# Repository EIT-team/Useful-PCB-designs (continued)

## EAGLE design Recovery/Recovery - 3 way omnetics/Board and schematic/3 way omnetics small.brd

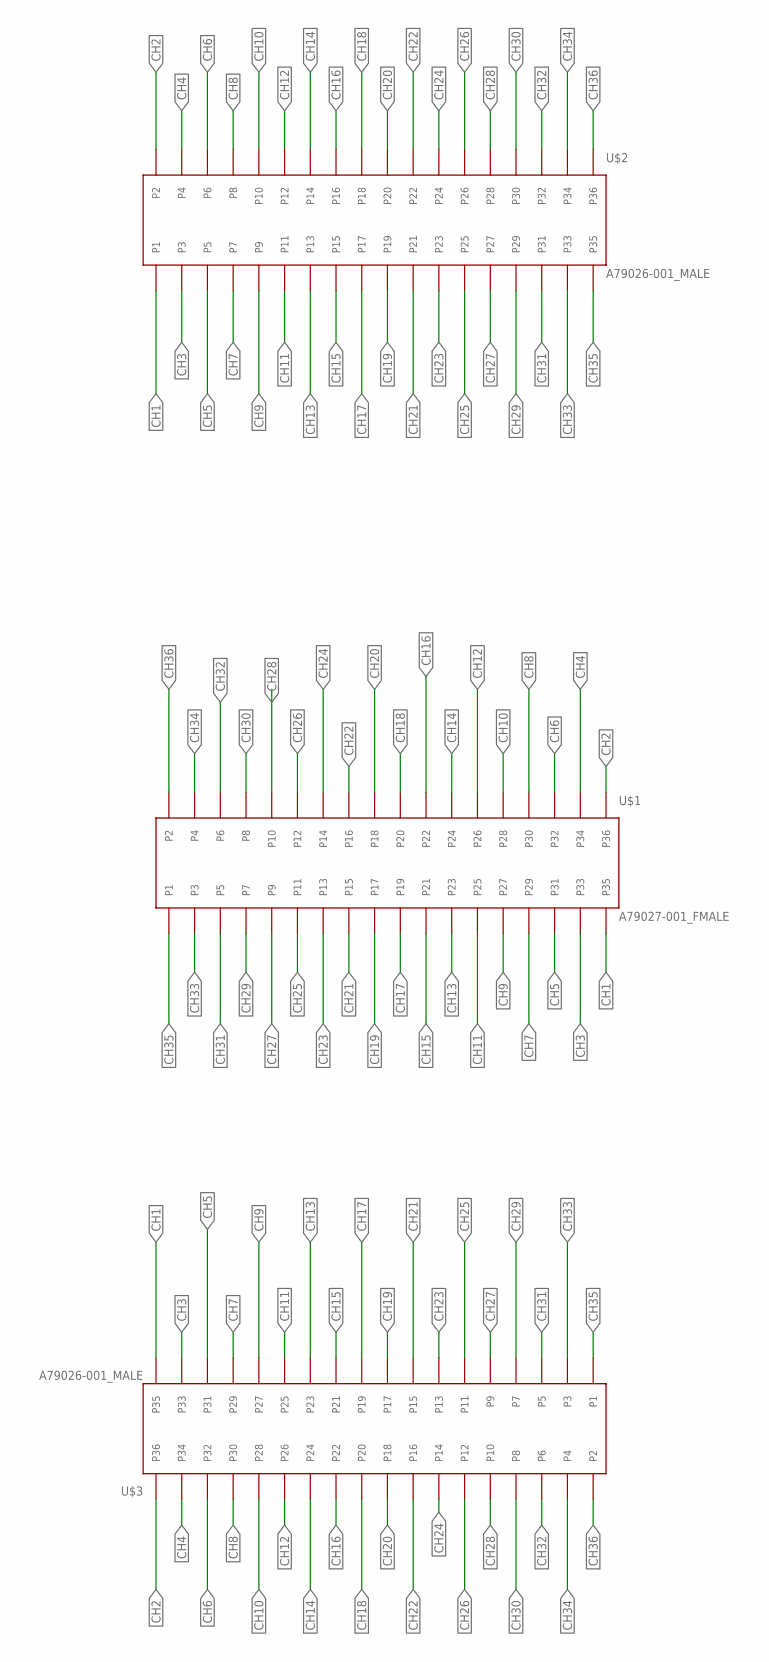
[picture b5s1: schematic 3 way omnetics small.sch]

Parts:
U$1: A79027-001_FMALE; A79026-001_MALE
U$2, U$3: A79026-001_MALE

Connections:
CH1: U$1.P35, U$2.P1, U$3.P35
CH2: U$1.P36, U$2.P2, U$3.P36
CH3: U$1.P33, U$2.P3, U$3.P33
CH4: U$1.P34, U$2.P4, U$3.P34
CH5: U$1.P31, U$2.P5, U$3.P31
CH6: U$1.P32, U$2.P6, U$3.P32
CH7: U$1.P29, U$2.P7, U$3.P29
CH8: U$1.P30, U$2.P8, U$3.P30
CH9: U$1.P27, U$2.P9, U$3.P27
CH10: U$1.P28, U$2.P10, U$3.P28
CH11: U$1.P25, U$2.P11, U$3.P25
CH12: U$1.P26, U$2.P12, U$3.P26
CH13: U$1.P23, U$2.P13, U$3.P23
CH14: U$1.P24, U$2.P14, U$3.P24
CH15: U$1.P21, U$2.P15, U$3.P21
CH16: U$1.P22, U$2.P16, U$3.P22
CH17: U$1.P19, U$2.P17, U$3.P19
CH18: U$1.P20, U$2.P18, U$3.P20
CH19: U$1.P17, U$2.P19, U$3.P17
CH20: U$1.P18, U$2.P20, U$3.P18
CH21: U$1.P15, U$2.P21, U$3.P15
CH22: U$1.P16, U$2.P22, U$3.P16
CH23: U$1.P13, U$2.P23, U$3.P13
CH24: U$1.P14, U$2.P24, U$3.P14
CH25: U$1.P11, U$2.P25, U$3.P11
CH26: U$1.P12, U$2.P26, U$3.P12
CH27: U$1.P9, U$2.P27, U$3.P9
CH28: U$1.P10, U$2.P28, U$3.P10
CH29: U$1.P7, U$2.P29, U$3.P7
CH30: U$1.P8, U$2.P30, U$3.P8
CH31: U$1.P5, U$2.P31, U$3.P5
CH32: U$1.P6, U$2.P32, U$3.P6
CH33: U$1.P3, U$2.P33, U$3.P3
CH34: U$1.P4, U$2.P34, U$3.P4
CH35: U$1.P1, U$2.P35, U$3.P1
CH36: U$1.P2, U$2.P36, U$3.P2

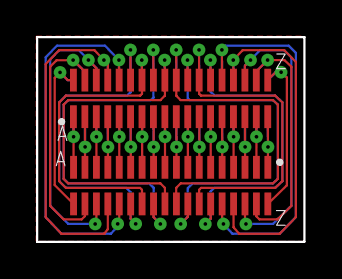
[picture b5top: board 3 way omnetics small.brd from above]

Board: 2 copper layers, 14.9 x 11.4 mm, 3 parts (1 on the bottom side), 36 nets.

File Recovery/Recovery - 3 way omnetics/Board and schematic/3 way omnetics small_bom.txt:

Partlist exported from C:/Users/Mayo/Documents/eagle/3 way omnetics/3 way omnetics small.sch at 07-Mar-18 1:59:39 PM

Part Value            Device           Package         Description 
U$1  A79027-001_FMALE A79027-001_FMALE A79026-001_MALE             
U$2  A79026-001_MALE  A79026-001_MALE  A79026-001_MALE             
U$3  A79026-001_MALE  A79026-001_MALE  A79026-001_MALE

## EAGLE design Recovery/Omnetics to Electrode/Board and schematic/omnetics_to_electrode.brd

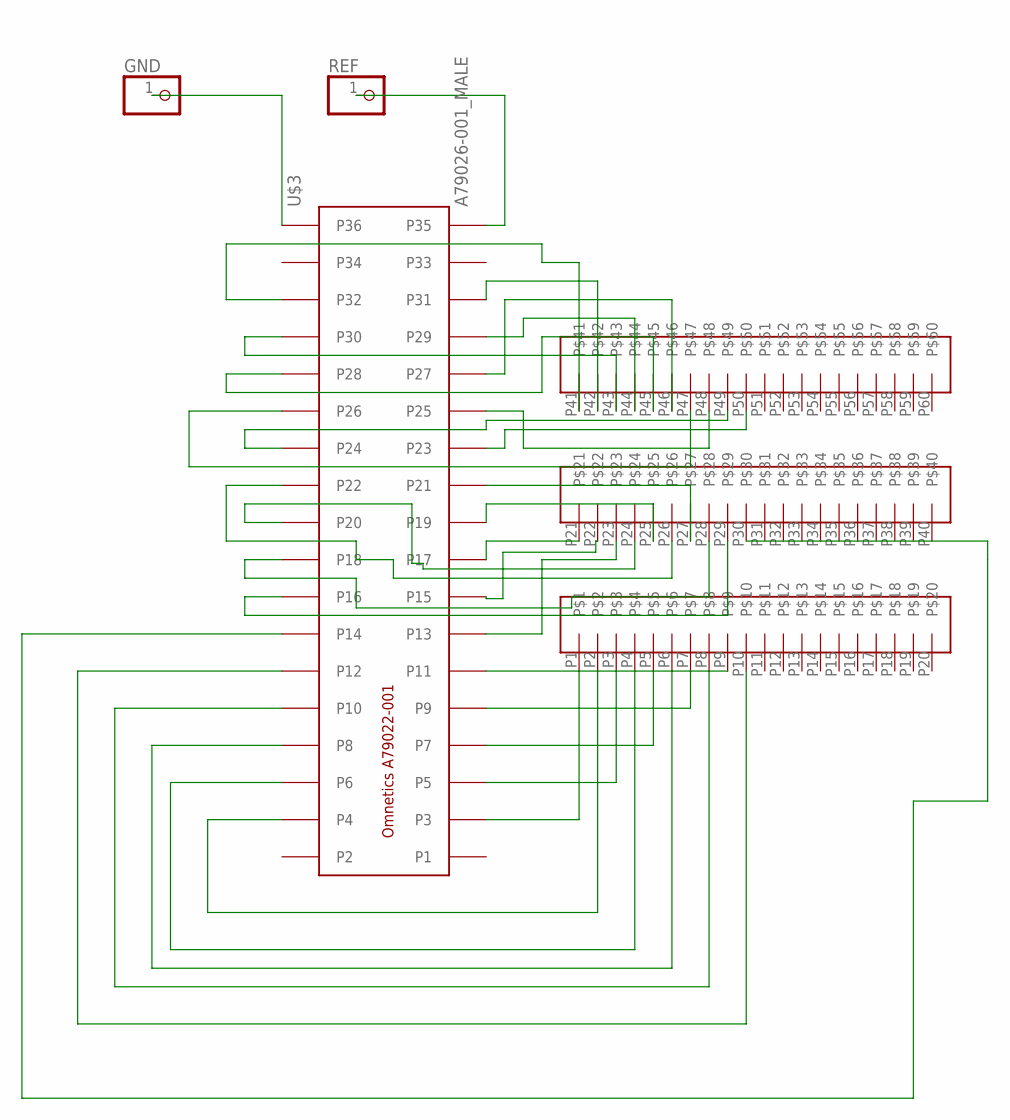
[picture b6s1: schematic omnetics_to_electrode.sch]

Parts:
GND: PINHD-1X1; 1X01
REF: PINHD-1X1; 1X01
U$1: ELEC_CONNECTOR
U$3: A79026-001_MALE

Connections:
GND: GND.1, U$3.P36
unnamed: U$1.P1, U$3.P3
unnamed: U$1.P2, U$3.P4
unnamed: U$1.P3, U$3.P5
unnamed: U$1.P4, U$3.P6
unnamed: U$1.P5, U$3.P7
unnamed: U$1.P6, U$3.P8
unnamed: U$1.P7, U$3.P9
unnamed: U$1.P8, U$3.P10
unnamed: U$1.P9, U$3.P11
unnamed: U$1.P10, U$3.P12
unnamed: U$1.P21, U$3.P17
unnamed: U$1.P23, U$3.P13
unnamed: U$1.P22, U$3.P15
unnamed: U$1.P30, U$3.P14
unnamed: U$1.P25, U$3.P19
unnamed: U$1.P27, U$3.P21
unnamed: U$1.P29, U$3.P16
unnamed: U$1.P28, U$3.P18
unnamed: U$1.P26, U$3.P22
unnamed: U$1.P24, U$3.P20
unnamed: U$1.P50, U$3.P23
unnamed: U$1.P49, U$3.P24
unnamed: U$1.P48, U$3.P25
unnamed: U$1.P47, U$3.P26
unnamed: U$1.P46, U$3.P27
unnamed: U$1.P45, U$3.P28
unnamed: U$1.P44, U$3.P29
unnamed: U$1.P43, U$3.P30
unnamed: U$1.P42, U$3.P31
unnamed: U$1.P41, U$3.P32
REF: REF.1, U$3.P35

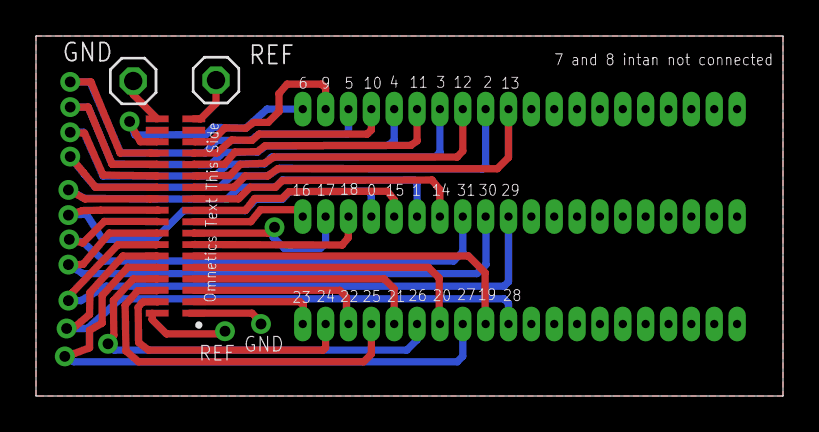
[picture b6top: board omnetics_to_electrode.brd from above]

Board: 2 copper layers, 41.5 x 20.0 mm, 4 parts (0 on the bottom side), 32 nets.

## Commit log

2019-02-01 various useful PCB designs
2020-10-06 updated Dsub to Actichamp connector board. PCBWAY gerbers
